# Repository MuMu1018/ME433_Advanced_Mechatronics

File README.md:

# Mengjiao_ME433_2017
Repository for ME 433 Advanced Mechatronics assignments and projects

Course Source: https://github.com/ndm736/ME433_2017/wiki

## HW1

HW1 assignment description [here](https://github.com/ndm736/ME433_2017/wiki/HW1). My homework folder [here](https://github.com/MuMu1018/Mengjiao_ME433_2017/tree/master/HW1).

This is my breadboard PIC32 circuit:

Test demo: a blinking LED (at 1 kHz), that stops when pushing and holding the USER pushbutton, and continues when releasings.

## HW2

HW2 assignment description [here](https://github.com/ndm736/ME433_2017/wiki/HW2). My homework folder [here](https://github.com/MuMu1018/Mengjiao_ME433_2017/tree/master/HW2).

This homework is the first half of [HW3](https://github.com/ndm736/ME433_2017/wiki/HW3). We use [Sparkfun Eagle Github libraries](https://github.com/sparkfun/SparkFun-Eagle-Libraries) to create our own libraries.

## HW3

HW3 assignment description [here](https://github.com/ndm736/ME433_2017/wiki/HW3). My homework folder [here](https://github.com/MuMu1018/Mengjiao_ME433_2017/tree/master/HW3).

We create a PCB of our PIC32 circuit, 5cm x 5cm, with header pins at specific locations. Do all of the error checking, generate the Gerber files. This is my design:

## HW4 - SPI DAC

HW4 assignment description [here](https://github.com/ndm736/ME433_2017/wiki/HW4). My homework folder [here](https://github.com/MuMu1018/Mengjiao_ME433_2017/tree/master/HW4).

Here's a schematic showing the connections between our PIC32 and this particular DAC ([the MCP4902](https://github.com/ndm736/ME433_2017/blob/master/mcp4902_spi-dac.pdf)) using SPI communication. The DAC outputs on pins V_OUTA (14) and V_OUTB (10).

The DAC outputs:

10Hz sine wave on VoutA + 5Hz triangle wave on VoutB:

10Hz sine wave on VoutA + 10Hz triangle wave on VoutB:

## HW5 - I2C pin expander

HW5 assignment description [here](https://github.com/ndm736/ME433_2017/wiki/HW5). My homework folder [here](https://github.com/MuMu1018/Mengjiao_ME433_2017/tree/master/HW5).

Here's a schematic showing the connections between our PIC32 and the MCP23008 I/O expander ([datasheet for MCP23008](https://github.com/ndm736/ME433_2017/blob/master/mcp23008_i2c-expander.pdf)) using I2C communication.

## HW6 - LCD printing

HW6 assignment description [here](https://github.com/ndm736/ME433_2017/wiki/HW6). My homework folder [here](https://github.com/MuMu1018/Mengjiao_ME433_2017/tree/master/HW6).

## HW7 - LCD control with IMU

Control the flowing bar on LCD screen by rotating LSM6DS33 breakout board, with I2C connection.

HW7 assignment description [here](https://github.com/ndm736/ME433_2017/wiki/HW7). My homework folder [here](https://github.com/MuMu1018/Mengjiao_ME433_2017/tree/master/HW7).

## HW8 - recreate HW7 project in MPLABX 

Use harmony to create a project for the PIC in MPLABX. 

HW8 assignment description [here](https://github.com/ndm736/ME433_2017/wiki/HW8). My homework folder [here](https://github.com/MuMu1018/Mengjiao_ME433_2017/tree/master/HW8).

## HW9 - USB communication between the PIC & PC

HW9 assignment description [here](https://github.com/ndm736/ME433_2017/wiki/HW9). My homework folder [here](https://github.com/MuMu1018/Mengjiao_ME433_2017/tree/master/HW9).

## HW10 - IIR, MAF and FIR low-pass filters

HW10 assignment description [here](https://github.com/ndm736/ME433_2017/wiki/HW10). My homework folder [here](https://github.com/MuMu1018/Mengjiao_ME433_2017/tree/master/HW10).

From the records, I find that IIR is better for tracking, while MAF and FIR filters are better in reducing noises.

## Final project

Final project assignment description [here](https://github.com/ndm736/ME433_2017/wiki/HW20). My Android code is in [this](https://github.com/MuMu1018/Mengjiao_ME433_2017/tree/master/HW20) folder.

Car body design with **SolidWorks**, and fabricate using **3D printing** and **laser cutting**:

+ Bracket (3D printing):

+ Wheels (3D printing):

+ Car body (Laser cutting):

+ Whole car:

+ Map info:

+ Video:

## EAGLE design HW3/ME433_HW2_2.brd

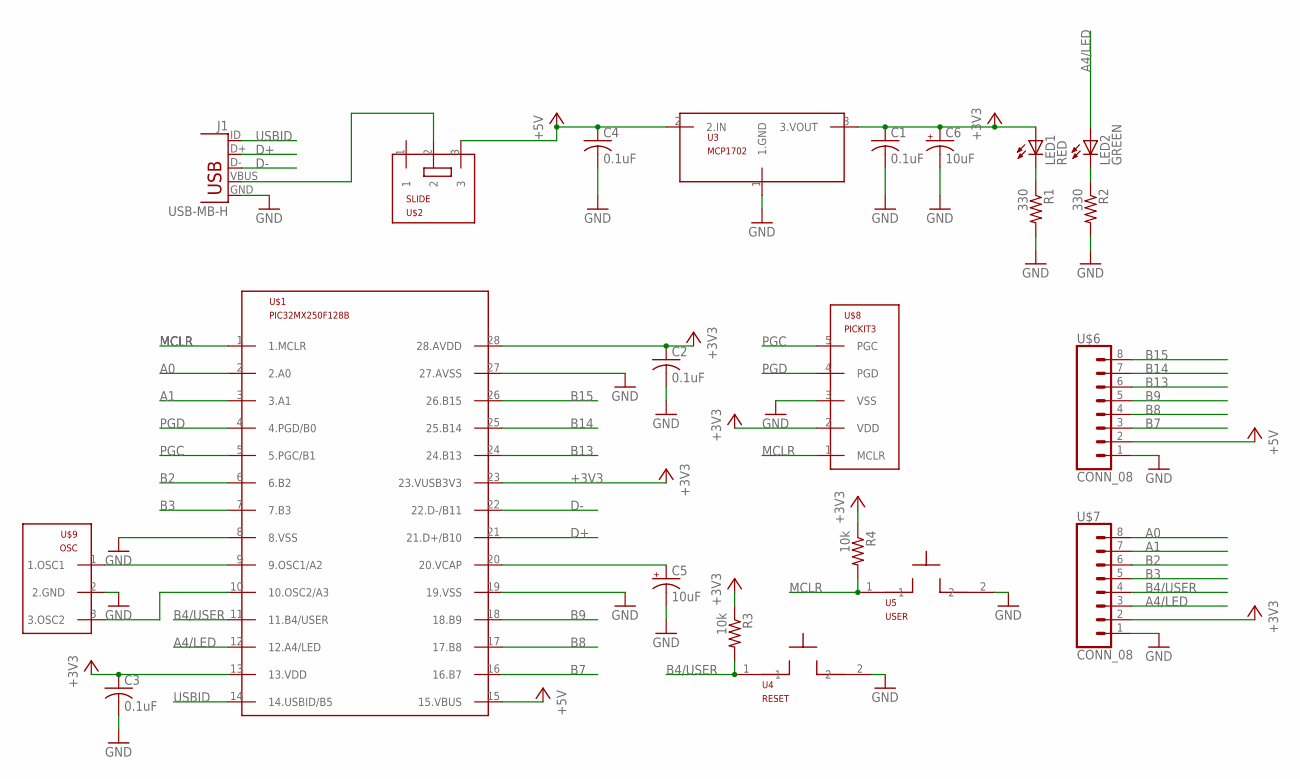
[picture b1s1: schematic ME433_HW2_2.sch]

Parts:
C1, C2, C3, C4: 0.1uF; C025-025X050
C5, C6: 10uF; B45181B
J1: USB-MB-H
LED1: RED; LED3MM
LED2: GREEN; LED3MM
R1, R2: 330; 0207/10
R3, R4: 10k; 0207/10
U3: MCP1702; TO92
U4: RESET; PB
U5: USER; PB
U$1: PIC32MX250F128B; DIL28-3
U$2: SLIDE
U$6, U$7: CONN_08; 1X08
U$8: PICKIT3; 1X05
U$9: OSC

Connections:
+3V3: C1.1, C2.1, C3.1, C6.+, LED1.A, R3.1, R4.1, U3.3 (3.VOUT), U$1.13 (13.VDD), U$1.23 (23.VUSB3V3), U$1.28 (28.AVDD), U$7.2, U$8.2 (VDD)
+5V: C4.1, U3.2 (2.IN), U$1.15 (15.VBUS), U$2.3, U$6.2
A0: U$1.2 (2.A0), U$7.8
A1: U$1.3 (3.A1), U$7.7
A4/LED: LED2.A, U$1.12 (12.A4/LED), U$7.3
B2: U$1.6 (6.B2), U$7.6
B3: U$1.7 (7.B3), U$7.5
B4/USER: R3.2, U4.1, U$1.11 (11.B4/USER), U$7.4
B7: U$1.16 (16.B7), U$6.3
B8: U$1.17 (17.B8), U$6.4
B9: U$1.18 (18.B9), U$6.5
B13: U$1.24 (24.B13), U$6.6
B14: U$1.25 (25.B14), U$6.7
B15: U$1.26 (26.B15), U$6.8
D+: J1.D+, U$1.21 (21.D+/B10)
D-: J1.D-, U$1.22 (22.D-/B11)
GND: C1.2, C2.2, C3.2, C4.2, C5.-, C6.-, J1.GND, R1.2, R2.2, U3.1 (1.GND), U4.2, U5.2, U$1.8 (8.VSS), U$1.19 (19.VSS), U$1.27 (27.AVSS), U$6.1, U$7.1, U$8.3 (VSS), U$9.2 (2.GND)
MCLR: R4.2, U5.1, U$1.1 (1.MCLR), U$8.1 (MCLR)
unnamed: LED1.K (C), R1.1
unnamed: LED2.K (C), R2.1
unnamed: U$1.10 (10.OSC2/A3), U$9.3 (3.OSC2)
unnamed: U$1.9 (9.OSC1/A2), U$9.1 (1.OSC1)
unnamed: C5.+, U$1.20 (20.VCAP)
PGC: U$1.5 (5.PGC/B1), U$8.5 (PGC)
PGD: U$1.4 (4.PGD/B0), U$8.4 (PGD)
USBID: J1.ID, U$1.14 (14.USBID/B5)
VBUS: J1.VBUS, U$2.2

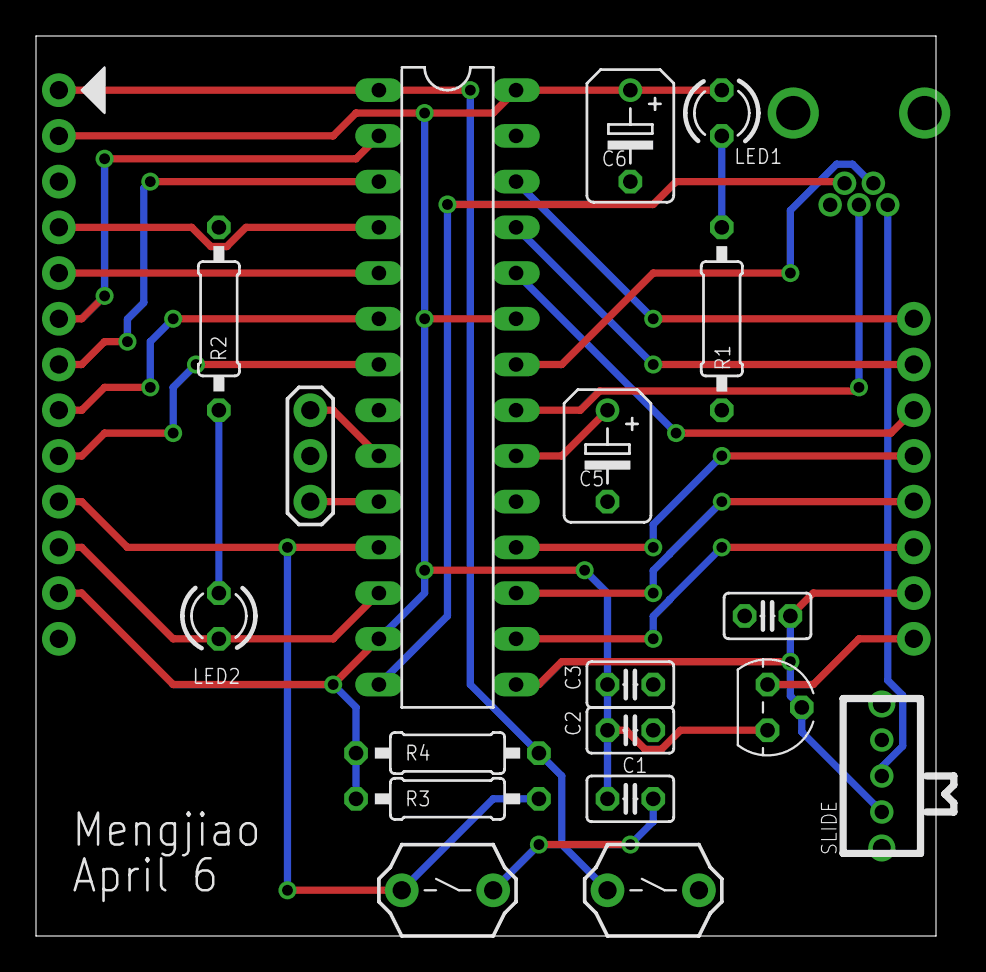
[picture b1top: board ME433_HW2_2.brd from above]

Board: 2 copper layers, 50.0 x 50.0 mm, 22 parts (0 on the bottom side), 27 nets.

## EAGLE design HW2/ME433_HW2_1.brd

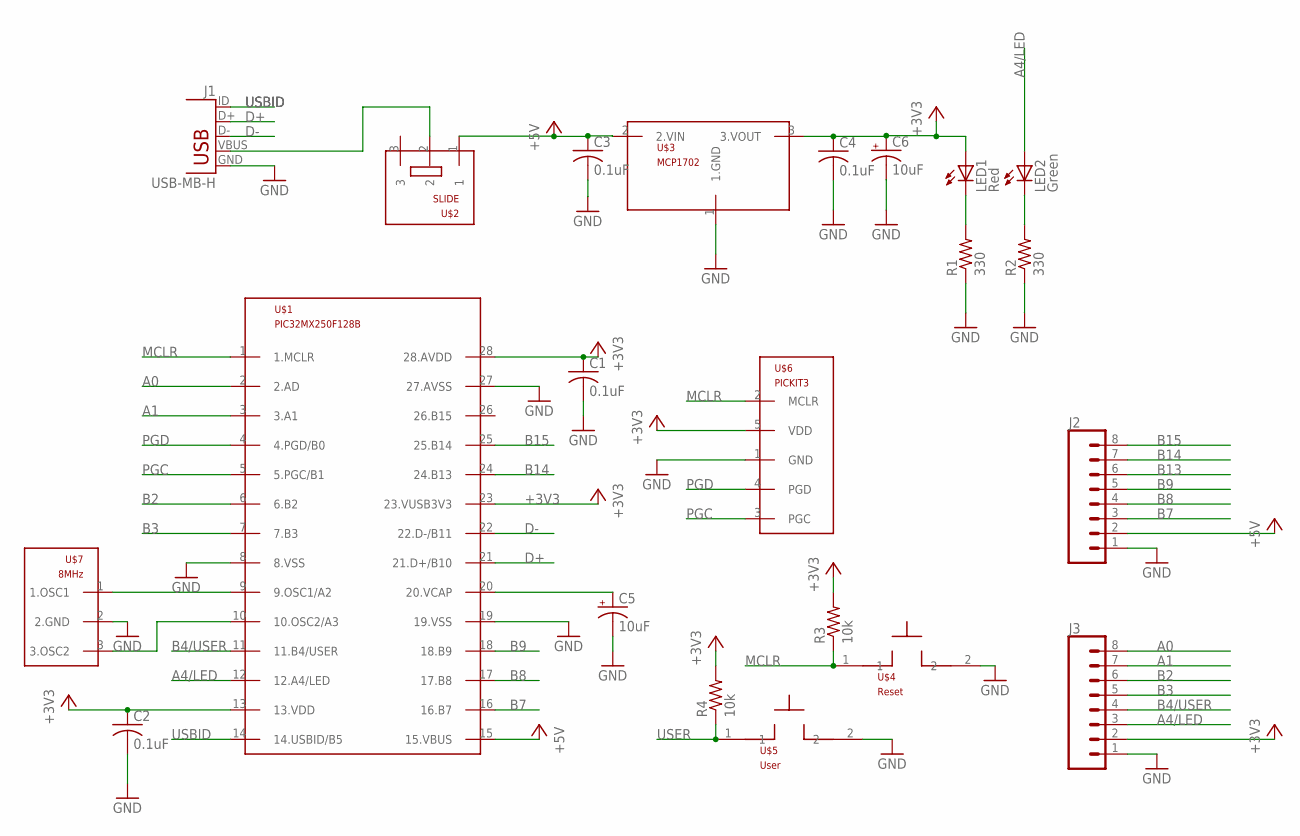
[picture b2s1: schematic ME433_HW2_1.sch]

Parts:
C1, C2, C3, C4: 0.1uF; C025-025X050
C5, C6: 10uF; B45181B
J1: USB-MB-H
J2, J3: CONN_08"; 1X08
LED1: Red; LED3MM
LED2: Green; LED3MM
R1, R2: 330; 0207/10
R3, R4: 10k; 0207/10
U$1: PIC32MX250F128B; DIL28-3
U$2: SLIDE
U$3: MCP1702; TO92
U$4: Reset; PB
U$5: User; PB
U$6: PICKIT3; 1X05
U$7: 8MHz; OSC

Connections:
+3V3: C1.1, C2.1, C4.1, C6.+, J3.2, LED1.A, R3.2, R4.2, U$1.13 (13.VDD), U$1.23 (23.VUSB3V3), U$1.28 (28.AVDD), U$3.3 (3.VOUT), U$6.5 (VDD)
+5V: C3.1, J2.2, U$1.15 (15.VBUS), U$2.1, U$3.2 (2.VIN)
A0: J3.8, U$1.2 (2.AD)
A1: J3.7, U$1.3 (3.A1)
A4/LED: J3.3, LED2.A, U$1.12 (12.A4/LED)
B2: J3.6, U$1.6 (6.B2)
B3: J3.5, U$1.7 (7.B3)
B4/USER: J3.4, U$1.11 (11.B4/USER)
B7: J2.3, U$1.16 (16.B7)
B8: J2.4, U$1.17 (17.B8)
B9: J2.5, U$1.18 (18.B9)
B13: J2.6
B14: J2.7, U$1.24 (24.B13)
B15: J2.8, U$1.25 (25.B14)
D+: J1.D+, U$1.21 (21.D+/B10)
D-: J1.D-, U$1.22 (22.D-/B11)
GND: C1.2, C2.2, C3.2, C4.2, C5.-, C6.-, J1.GND, J2.1, J3.1, R1.1, R2.1, U$1.8 (8.VSS), U$1.19 (19.VSS), U$1.27 (27.AVSS), U$3.1 (1.GND), U$4.2, U$5.2, U$6.1 (GND), U$7.2 (2.GND)
MCLR: R3.1, U$1.1 (1.MCLR), U$4.1, U$6.2 (MCLR)
unnamed: LED1.K (C), R1.2
unnamed: LED2.K (C), R2.2
unnamed: U$1.9 (9.OSC1/A2), U$7.1 (1.OSC1)
unnamed: U$1.10 (10.OSC2/A3), U$7.3 (3.OSC2)
unnamed: C5.+, U$1.20 (20.VCAP)
PGC: U$1.5 (5.PGC/B1), U$6.3 (PGC)
PGD: U$1.4 (4.PGD/B0), U$6.4 (PGD)
USBID: J1.ID, U$1.14 (14.USBID/B5)
USER: R4.1, U$5.1
VBUS: J1.VBUS, U$2.2

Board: 2 copper layers, 22 parts (0 on the bottom side), 27 nets, no tracks yet.

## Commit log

2017-03-30 HW1 finish
    Use LATxINV is better than set pin to 1 and then set it to 0 every
    loop, otherwise the LED will always be off when push button
2017-03-30 HW1 - original codes
    The original one used LAT set RA4 twice (turn on/off) every while loop,
    when the button was not pushed. Thus the LED will always be off when
    push the button.
2017-03-30 HW1 - Original codes
    LED will always be off when pushing the button.
2017-03-30 HW1 - Final codes
    That is fine, same with first one.
    I need time to get used to Github >.<
2017-03-30 PWM problems
    It works well when push the button, but the wave picture shows in
    nScope looks bad.
2017-03-30 This is the REAL final codes!
    It’s amazing! Last “Final codes” has problems, but it run well!
    In line 67, I used if to do the counting, and it should not work, but
    it did!
    Okay, I C. It will not show any problem if I just check the button, and
    not check the nScope graph!
2017-03-30 Pictures for homework
    Not much difference between oscillations & clean voltage
2017-04-04 ME433_HW2
    Follow the tutorial. Get familiar with Eagle.
2017-04-05 Redo HW2
    Correct two mistakes in the schematic: (1) mirror the SLIDE to make
    sure input and output connect to the right pin. (2) correct the pin
    name and connection of PICKIT3
2017-04-07 HW3
    Do it twice..If have more time, I want to do it third time.
2017-04-26 Start SPI
2017-04-28 HW4
    SPI communication
2017-04-28 HW4 SPI communication
    Use SPI1 to talk to the DAC.
    The DAC outputs a 10Hz sine wave on VoutA and a 5Hz/10Hz triangle wave
    on VoutB.
2017-04-28 Week4 SPI communication
    Make library: spi.c and spi.h
2017-05-04 HW5
    I2C - if GP7 is high, output high on GP0, otherwise output low
2017-05-04 HW6 LCD-HelloWorld!
    I set screen as 132*132, instead of 128*128, to clear the mess margin.
2017-05-05 HW6
    HelloWorld!
2017-05-08 HW7
    Help functions
2017-05-09 HW7 IMU
    Use accelerometers to control the gravity bar print on LCD screen
2017-05-09 Homework update
2017-05-09 HW8 Harmony installation
    HW7 code works well with Harmony
2017-05-09 Software update
    Update MPLAB X IDE v3.55 to v3.60
2017-05-09 Home work update
2017-05-10 HW9 - a USB CDC Harmony project
2017-05-18 HW10 - MAF, IIR, and FIR low-pass filters
2017-05-18 HW10 - MAF, IIR, and FIR low-pass filters
2017-05-18 Software update
2017-05-18 HW10 - MAF, IIR, and FIR low-pass filters
    Get trouble with putting data into matrix in Matlab
2017-05-22 HW11 - HID
    USB mouse control
2017-05-23 HW12 - Android slider app
2017-05-23 HW13 - Android app: identifies green objects
2017-06-05 HW14 - Android USB
2017-06-06 HW18 - Motors and Control
    Can set speed and direction to both motors through keyboard
2017-06-09 final project
2017-06-09 HW15 - Wheel and 3sided-box Design
2017-06-09 HW16 - 3D printing and assembling wheel
2017-06-09 HW16 - 3D printed and assembled wheel
2017-06-09 HW17 - Laser cut box (assembled)
2017-06-09 Final project - Mobile Robot Design
    Android app controlled, tracing the colored line with a live camera of an android phone.
2017-09-06 PCB board_screenshot
2017-09-06 PCB board design
2017-09-06 update sreenshot
2018-05-12 add descriptions for this project
2018-05-12 modify pictures of car design
2018-05-12 resize the pictures of car design
2018-05-12 add screenshot of carbody design
2018-05-12 update screenshot of carbody design
2018-05-12 add map picture and video of car testing
2018-05-13 add map info
2018-05-13 update map info
